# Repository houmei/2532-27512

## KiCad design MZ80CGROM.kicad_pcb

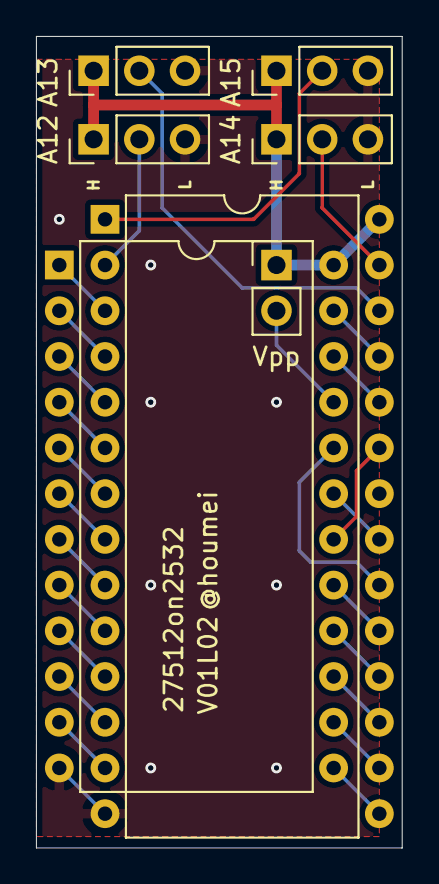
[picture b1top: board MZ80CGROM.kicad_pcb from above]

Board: 2 copper layers, 20.3 x 45.1 mm, 7 parts (0 on the bottom side), 28 nets.

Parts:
J1: AD12; PinHeader_1x03_P2.54mm_Vertical
J2: AD13; PinHeader_1x03_P2.54mm_Vertical
J3: AD14; PinHeader_1x03_P2.54mm_Vertical
J4: AD15; PinHeader_1x03_P2.54mm_Vertical
J5: Vpp2532; PinHeader_1x02_P2.54mm_Vertical
U1: 27512; DIP-28_W15.24mm
U2: 2532; DIP-24_W15.24mm

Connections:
A0: U1.10, U2.8
A1: U1.9, U2.7
A2: U1.8, U2.6
A3: U1.7, U2.5
A4: U1.6, U2.4
A5: U1.5, U2.3
A6: U1.4, U2.2
A7: U1.3, U2.1
A8: U1.25, U2.23
A9: U1.24, U2.22
A10: U1.21, U2.19
A11: U1.23, U2.18
D0: U1.11, U2.9
D1: U1.12, U2.10
D2: U1.13, U2.11
D3: U1.15, U2.13
D4: U1.16, U2.14
D5: U1.17, U2.15
D6: U1.18, U2.16
D7: U1.19, U2.17
unnamed: J1.2, U1.2
unnamed: J2.2, U1.26
unnamed: J3.2, U1.27
unnamed: J4.2, U1.1
Vdd: J1.1, J2.1, J3.1, J4.1, J5.1, U1.28, U2.24
Vpp: J5.2, U2.21
Vss: J1.3, J2.3, J3.3, J4.3, U1.14, U1.22, U2.12
~CE: U1.20, U2.20

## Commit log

2022-12-27 fix symbol path
2022-12-27 add Symbol folder
